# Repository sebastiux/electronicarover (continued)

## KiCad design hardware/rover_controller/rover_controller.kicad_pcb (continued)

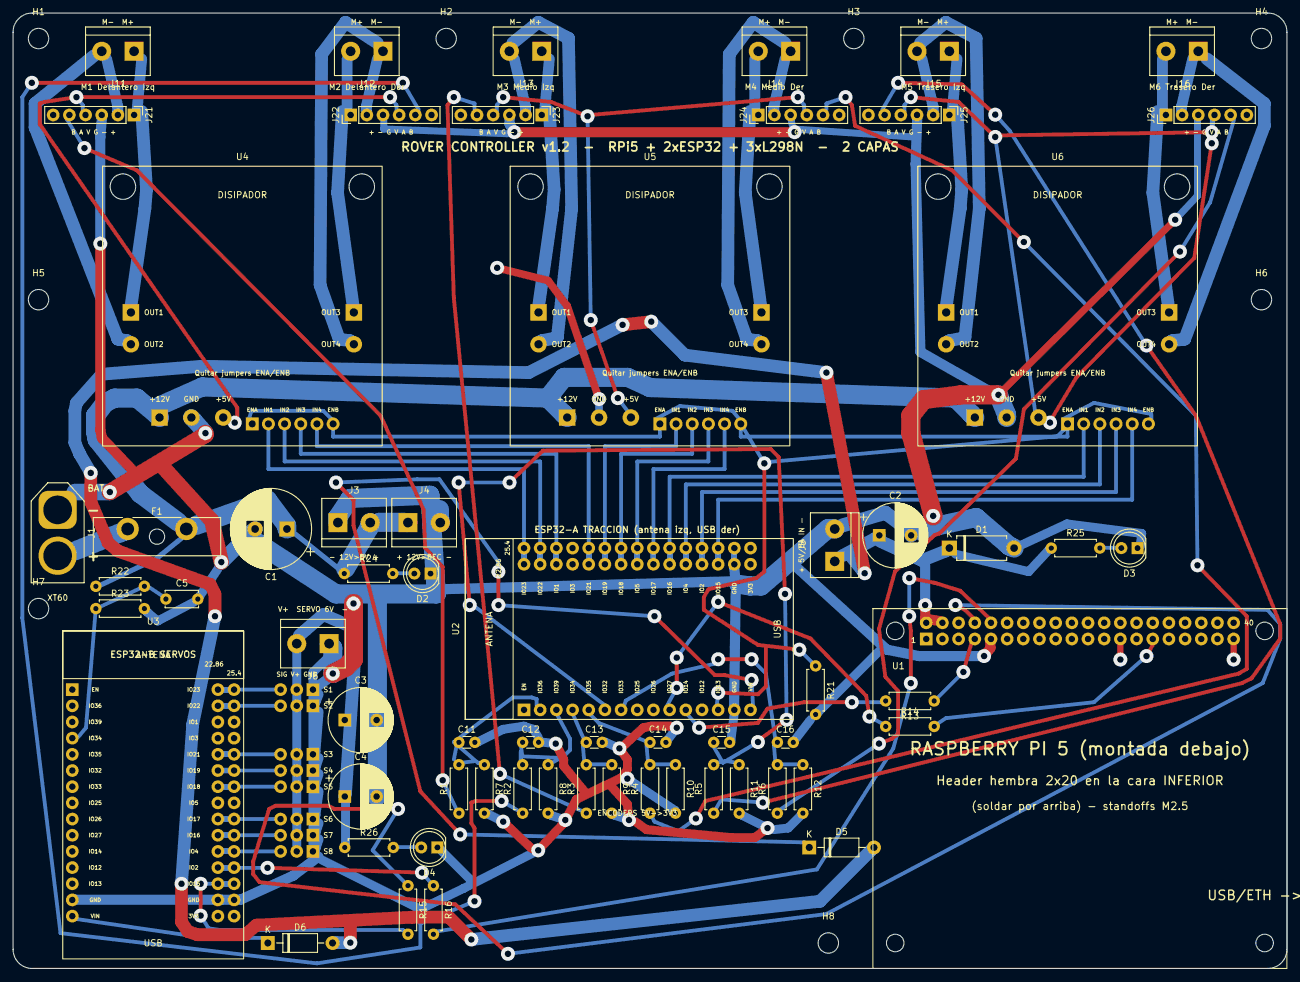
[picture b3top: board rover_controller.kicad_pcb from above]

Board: 2 copper layers, 200.0 x 150.0 mm, 79 parts (0 on the bottom side), 67 nets.

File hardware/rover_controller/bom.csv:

Cant;Referencias;Valor;Footprint;Parte sugerida;Descripcion
1;C1;1000uF 25V;Capacitor_THT:CP_Radial_D12.5mm_P5.00mm;1000uF 25V;Bulk VBAT
3;C2,C3,C4;1000uF 10V;Capacitor_THT:CP_Radial_D10.0mm_P5.00mm;1000uF 10V;Bulk 5V
1;C5;100nF;Capacitor_THT:C_Disc_D5.0mm_W2.5mm_P5.00mm;100nF;Filtro ADC VBAT
1;D1;SA5.0A;Diode_THT:D_DO-15_P10.16mm_Horizontal;SA5.0A DO-15;TVS 5V (proteccion Pi)
1;D2;LED rojo 12V;LED_THT:LED_D5.0mm;LED 5mm THT tradicional (rojo);Indicador 12V
1;D3;LED verde 5V;LED_THT:LED_D5.0mm;LED 5mm THT tradicional (verde);Indicador 5V
1;D4;LED azul SERVO;LED_THT:LED_D5.0mm;LED 5mm THT tradicional (azul);Indicador rail servos
1;F1;ATO 15A;Fuse:Fuseholder_Blade_ATO_Littelfuse_Pudenz_2_Pin;Littelfuse/Pudenz 2 pin ATO holder;Portafusible ATO para PCB + fusible 15A
8;H1,H2,H3,H4,H5,H6,H7,H8;M3;MountingHole:MountingHole_3.2mm_M3;M3;Agujero de montaje M3
1;J1;XT60 BAT 12V;Connector_AMASS:AMASS_XT60-M_1x02_P7.20mm_Vertical;AMASS XT60 macho (copas para soldar) / XT60-M;Conector XT60 macho para bateria LiPo 3S (lado biselado = -)
1;J11;Motor M1;TerminalBlock:TerminalBlock_bornier-2_P5.08mm;KF301-2P / DG301 5.08mm;Bornera 2P 5.08mm motor M1 (Delantero Izq)
1;J12;Motor M2;TerminalBlock:TerminalBlock_bornier-2_P5.08mm;KF301-2P / DG301 5.08mm;Bornera 2P 5.08mm motor M2 (Delantero Der)
1;J13;Motor M3;TerminalBlock:TerminalBlock_bornier-2_P5.08mm;KF301-2P / DG301 5.08mm;Bornera 2P 5.08mm motor M3 (Medio Izq)
1;J14;Motor M4;TerminalBlock:TerminalBlock_bornier-2_P5.08mm;KF301-2P / DG301 5.08mm;Bornera 2P 5.08mm motor M4 (Medio Der)
1;J15;Motor M5;TerminalBlock:TerminalBlock_bornier-2_P5.08mm;KF301-2P / DG301 5.08mm;Bornera 2P 5.08mm motor M5 (Trasero Izq)
1;J16;Motor M6;TerminalBlock:TerminalBlock_bornier-2_P5.08mm;KF301-2P / DG301 5.08mm;Bornera 2P 5.08mm motor M6 (Trasero Der)
1;J21;Pololu37D_M1;Connector_PinHeader_2.54mm:PinHeader_1x06_P2.54mm_Vertical;Header macho 1x6 2.54mm;Header 1x6 macho: cable Pololu 37D (M+, M-, GND, VCC, A, B)
1;J22;Pololu37D_M2;Connector_PinHeader_2.54mm:PinHeader_1x06_P2.54mm_Vertical;Header macho 1x6 2.54mm;Header 1x6 macho: cable Pololu 37D (M+, M-, GND, VCC, A, B)
1;J23;Pololu37D_M3;Connector_PinHeader_2.54mm:PinHeader_1x06_P2.54mm_Vertical;Header macho 1x6 2.54mm;Header 1x6 macho: cable Pololu 37D (M+, M-, GND, VCC, A, B)
1;J24;Pololu37D_M4;Connector_PinHeader_2.54mm:PinHeader_1x06_P2.54mm_Vertical;Header macho 1x6 2.54mm;Header 1x6 macho: cable Pololu 37D (M+, M-, GND, VCC, A, B)
1;J25;Pololu37D_M5;Connector_PinHeader_2.54mm:PinHeader_1x06_P2.54mm_Vertical;Header macho 1x6 2.54mm;Header 1x6 macho: cable Pololu 37D (M+, M-, GND, VCC, A, B)
1;J26;Pololu37D_M6;Connector_PinHeader_2.54mm:PinHeader_1x06_P2.54mm_Vertical;Header macho 1x6 2.54mm;Header 1x6 macho: cable Pololu 37D (M+, M-, GND, VCC, A, B)
1;J3;12V OUT -> buck 5V;TerminalBlock:TerminalBlock_bornier-2_P5.08mm;KF301-2P 5.08mm;Salida 12V protegida hacia el step-down de 5V/5A
1;J31;SERVO1;rover:Servo_Header_1x03;Header macho 1x3 2.54mm;Servo 1 - Direccion DI (GND, V+, SIG)
1;J32;SERVO2;rover:Servo_Header_1x03;Header macho 1x3 2.54mm;Servo 2 - Direccion DD (GND, V+, SIG)
1;J33;SERVO3;rover:Servo_Header_1x03;Header macho 1x3 2.54mm;Servo 3 - Direccion TI (GND, V+, SIG)
1;J34;SERVO4;rover:Servo_Header_1x03;Header macho 1x3 2.54mm;Servo 4 - Direccion TD (GND, V+, SIG)
1;J35;SERVO5;rover:Servo_Header_1x03;Header macho 1x3 2.54mm;Servo 5 - Brazo base (GND, V+, SIG)
1;J36;SERVO6;rover:Servo_Header_1x03;Header macho 1x3 2.54mm;Servo 6 - Brazo hombro (GND, V+, SIG)
1;J37;SERVO7;rover:Servo_Header_1x03;Header macho 1x3 2.54mm;Servo 7 - Brazo pinza (GND, V+, SIG)
1;J38;SERVO8;rover:Servo_Header_1x03;Header macho 1x3 2.54mm;Servo 8 - Reserva (GND, V+, SIG)
1;J4;12V OUT -> BEC servos;TerminalBlock:TerminalBlock_bornier-2_P5.08mm;KF301-2P 5.08mm;Salida 12V protegida hacia el BEC de servos 6V
1;J43;AUX RPi (I2C);Connector_PinHeader_2.54mm:PinHeader_1x08_P2.54mm_Vertical;Header macho 1x8;Header auxiliar Raspberry Pi (I2C + GPIO)
1;J5;5V IN (buck 5V 5A);TerminalBlock:TerminalBlock_bornier-2_P5.08mm;KF301-2P 5.08mm;Entrada 5V/5A desde step-down (alimenta Pi 5 y ESP32)
1;J6;SERVO PWR IN (6V);TerminalBlock:TerminalBlock_bornier-2_P5.08mm;KF301-2P 5.08mm;Entrada BEC servos 6V
7;R1,R2,R3,R4,R5,R6,R21;10k;Resistor_THT:R_Axial_DIN0207_L6.3mm_D2.5mm_P7.62mm_Horizontal;Resistencia 10k 1/4W (0.25W) THT pelicula metalica/carbon;Divisor encoder (serie)
4;R13,R14,R15,R16;1k;Resistor_THT:R_Axial_DIN0207_L6.3mm_D2.5mm_P7.62mm_Horizontal;Resistencia 1k 1/4W (0.25W) THT pelicula metalica/carbon;Serie UART Pi TXD2 -> ESP32-A RX
1;R22;100k;Resistor_THT:R_Axial_DIN0207_L6.3mm_D2.5mm_P7.62mm_Horizontal;Resistencia 100k 1/4W (0.25W) THT pelicula metalica/carbon;Divisor VBAT (alto)
1;R23;27k;Resistor_THT:R_Axial_DIN0207_L6.3mm_D2.5mm_P7.62mm_Horizontal;Resistencia 27k 1/4W (0.25W) THT pelicula metalica/carbon;Divisor VBAT (bajo)
1;R24;2.2k;Resistor_THT:R_Axial_DIN0207_L6.3mm_D2.5mm_P7.62mm_Horizontal;Resistencia 2.2k 1/4W (0.25W) THT pelicula metalica/carbon;Resistencia LED 12V
1;R25;330;Resistor_THT:R_Axial_DIN0207_L6.3mm_D2.5mm_P7.62mm_Horizontal;Resistencia 330 1/4W (0.25W) THT pelicula metalica/carbon;Resistencia LED 5V
1;R26;470;Resistor_THT:R_Axial_DIN0207_L6.3mm_D2.5mm_P7.62mm_Horizontal;Resistencia 470 1/4W (0.25W) THT pelicula metalica/carbon;Resistencia LED servos
6;R7,R8,R9,R10,R11,R12;20k;Resistor_THT:R_Axial_DIN0207_L6.3mm_D2.5mm_P7.62mm_Horizontal;Resistencia 20k 1/4W (0.25W) THT pelicula metalica/carbon;Divisor encoder (a GND)
1;U1;RaspberryPi5_GPIO;rover:RPi5_HAT_Header_2x20;Stacking header 2x20 2.54mm pines largos;Stacking header 2x20 de pines largos (Pi 5 debajo, soldar por la cara de cobre)
1;U2;ESP32-A_Traccion;rover:ESP32_DevKitV1_30P_DualPitch;ESP32 DevKit V1 CP2102 + 2x header hembra 1x15;ESP32 DevKit V1 30 pines sobre 2x header hembra 1x15
1;U3;ESP32-B_Servos;rover:ESP32_DevKitV1_30P_DualPitch;ESP32 DevKit V1 CP2102 + 2x header hembra 1x15;ESP32 DevKit V1 30 pines sobre 2x header hembra 1x15
3;U4,U5,U6;L298N_Module;rover:L298N_Module_Pins;Modulo puente H L298N (HW-095);Modulo L298N (bornas sustituidas por pines, quitar jumpers ENA/ENB, dejar el jumper 5V-EN: su +5V alimenta los encoders)

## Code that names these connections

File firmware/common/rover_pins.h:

// rover_pins.h - Mapa de pines de la PCB Rover Controller v1.0 (2 capas)
// Fuente: hardware/tools/rover_design.py (mantener sincronizado).
//
// Las asignaciones estan elegidas para que el ruteo de la PCB quede limpio:
// el orden fisico de los pines de la ESP32 coincide con el orden de los
// destinos. Los UART del ESP32 se remapean (Serial2.begin(baud, cfg, RX, TX)).
#pragma once

// ===========================================================================
// ESP32-A : TRACCION (U2, montada horizontal bajo los L298N)
// ===========================================================================
#if defined(ROVER_ESP32_A)

// Habilitacion global de los 6 canales (ENA/ENB de los 3 L298N).
// Pull-down de 10k: los motores quedan APAGADOS hasta que el firmware ponga
// este pin en HIGH (los IN pueden "parpadear" durante el arranque sin efecto).
#define PIN_MOTOR_EN 13

// Control por motor: PWM en un IN y el otro en LOW (EN = HIGH via MOTOR_EN).
//   avance:  IN_A = PWM, IN_B = 0      reversa: IN_A = 0, IN_B = PWM
//   freno:   IN_A = 1,   IN_B = 1      libre:   MOTOR_EN = 0 (afecta a todos)
//                          {IN_A, IN_B}
#define PIN_M1 {23, 22} // U4 IN1/IN2 -> OUT1/OUT2  Delantero Izq
#define PIN_M2 {1, 21}  // U4 IN3/IN4 -> OUT3/OUT4  Delantero Der  (GPIO1 = TX0!)
#define PIN_M3 {19, 18} // U5 IN1/IN2               Medio Izq
#define PIN_M4 {5, 17}  // U5 IN3/IN4               Medio Der
#define PIN_M5 {16, 4}  // U6 IN1/IN2               Trasero Izq
#define PIN_M6 {2, 15}  // U6 IN3/IN4               Trasero Der
// OJO: GPIO1 (TX0) maneja un IN del L298N: NO uses Serial.print() en la
// ESP32-A una vez arrancado el control (usa Serial2 hacia la Pi para telemetria).

// Encoders Pololu 37D, canal A (divisor 10k/20k -> 3.3V). 16 pulsos por vuelta
// del motor por canal x 30 = 480 flancos de subida por vuelta de rueda.
// El canal B no esta cableado; el sentido se toma del comando.
#define PIN_ENC1_A 36
#define PIN_ENC2_A 39
#define PIN_ENC3_A 34
#define PIN_ENC4_A 35
#define PIN_ENC5_A 32
#define PIN_ENC6_A 33

// UART <-> Raspberry Pi (Pi UART2: GPIO4 TX / GPIO5 RX, /dev/ttyAMA2)
#define PIN_UART_RX 14
#define PIN_UART_TX 27
// Serial2.begin(115200, SERIAL_8N1, PIN_UART_RX, PIN_UART_TX);

#endif

// ===========================================================================
// ESP32-B : SERVOS + BRAZO (U3, vertical a la izquierda)
// ===========================================================================
#if defined(ROVER_ESP32_B)

#define PIN_SERVO1 23 // Direccion delantera izq
#define PIN_SERVO2 22 // Direccion delantera der
#define PIN_SERVO3 21 // Direccion trasera izq
#define PIN_SERVO4 19 // Direccion trasera der
#define PIN_SERVO5 18 // Brazo base
#define PIN_SERVO6 17 // Brazo hombro
#define PIN_SERVO7 16 // Brazo pinza
#define PIN_SERVO8 4  // Brazo codo/muneca

// Voltaje de bateria: divisor 100k / 27k (VBAT = Vadc * 127 / 27)
#define PIN_VBAT_SENSE 34
#define VBAT_DIVIDER_RATIO (127.0f / 27.0f)

// UART <-> Raspberry Pi (Pi UART0: GPIO14 TX / GPIO15 RX, /dev/ttyAMA0)
#define PIN_UART_RX 15
#define PIN_UART_TX 2   // GPIO2 tambien enciende el LED azul de la placa
// Serial2.begin(115200, SERIAL_8N1, PIN_UART_RX, PIN_UART_TX);

#endif

// ===========================================================================
// RASPBERRY PI 5 (numeros BCM) - /boot/firmware/config.txt:
//   dtoverlay=uart0-pi5   # GPIO14/15 -> ESP32-B  (/dev/ttyAMA0)
//   dtoverlay=uart2-pi5   # GPIO4/5   -> ESP32-A  (/dev/ttyAMA2)
//   usb_max_current_enable=1
// El resto de los GPIO quedan libres: los pines largos del stacking header
// sobresalen por arriba de la PCB y se puede conectar ahi con cables Dupont.
// ===========================================================================

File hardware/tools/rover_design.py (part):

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    # Otras fuentes dan 36.6 / 37 / 37.2 mm. Barreno de 4.0 mm centrado a +-18.75:
    # con tornillo M3 acepta cualquier separacion entre 36.5 y 38.5 mm.
    # Solo los 2 barrenos del lado del disipador: el lado de los pines queda fijo por
    # los 13 pines soldados (y ahi los barrenos de 4 mm cortarian la pista MOTOR_EN).
    "size": 43.9,
    "mount_holes": [(-18.75, -18.75), (18.75, -18.75)],
    "mount_drill": 4.0,
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}
RPI_PINS = {
    1: "3V3", 2: "5V", 3: "GPIO2/SDA", 4: "5V", 5: "GPIO3/SCL", 6: "GND",
    7: "GPIO4/TXD2", 8: "GPIO14/TXD0", 9: "GND", 10: "GPIO15/RXD0",
    11: "GPIO17", 12: "GPIO18", 13: "GPIO27", 14: "GND", 15: "GPIO22",
    16: "GPIO23", 17: "3V3", 18: "GPIO24", 19: "GPIO10", 20: "GND",
    21: "GPIO9", 22: "GPIO25", 23: "GPIO11", 24: "GPIO8", 25: "GND",
    26: "GPIO7", 27: "ID_SD", 28: "ID_SC", 29: "GPIO5/RXD2", 30: "GND",
    31: "GPIO6", 32: "GPIO12", 33: "GPIO13", 34: "GND", 35: "GPIO19",
    36: "GPIO16", 37: "GPIO26", 38: "GPIO20", 39: "GND", 40: "GPIO21",
}
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
    # ======================= ESP32-A (traccion) =============================
    espa = {i: None for i in range(1, 31)}
    espa[esp_pin_number("VIN")] = "VIN_A"     # via diodo D5 (evita retroalimentar por USB)
    espa[14] = "GND"
    espa[29] = "GND"
    for k, gp in ESPA_IN.items():
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            espa[esp_pin_number(g)] = "U%d_IN%d" % (k + 4, j + 1)
    for m, g in ESPA_ENC.items():
        espa[esp_pin_number(g)] = "ENC%d_A" % m
    espa[esp_pin_number(ESPA_MOTOR_EN)] = "MOTOR_EN"
    espa[esp_pin_number(ESPA_UART_TX)] = "ESPA_TX"
    espa[esp_pin_number(ESPA_UART_RX)] = "ESPA_RX"
    add("U2", "ESP32-A_Traccion", "rover:ESP32_DevKitV1_30P", "rover:ESP32_DevKitV1_30P_DualPitch",
        espa, ESPA_POS, (330.2, 76.2),
        desc="ESP32 DevKit V1 30 pines sobre 2x header hembra 1x15",
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
    # ======================= ESP32-B (servos) ===============================
    espb = {i: None for i in range(1, 31)}
    espb[esp_pin_number("VIN")] = "VIN_B"     # via diodo D6
    espb[14] = "GND"
    espb[29] = "GND"
    for n, (g, _) in SERVOS.items():
        espb[esp_pin_number(g)] = "SERVO%d" % n
    espb[esp_pin_number(ESPB_VBAT)] = "VBAT_SENSE"
    espb[esp_pin_number(ESPB_UART_TX)] = "ESPB_TX"
    espb[esp_pin_number(ESPB_UART_RX)] = "ESPB_RX"
    add("U3", "ESP32-B_Servos", "rover:ESP32_DevKitV1_30P", "rover:ESP32_DevKitV1_30P_DualPitch",
        espb, ESPB_POS, (457.2, 76.2),
        desc="ESP32 DevKit V1 30 pines sobre 2x header hembra 1x15",
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
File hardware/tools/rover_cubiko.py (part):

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    for n in (9, 25, 39):                     # GND de la fila interior (salen hacia abajo)
        pi[n] = "GND"
    pi[7], pi[29] = "PI_TXD2", "PI_RXD2"      # UART2 -> ESP32-A
    pi[32], pi[33] = "PI_TXD4", "PI_RXD4"     # UART4 (GPIO12/13, /dev/ttyAMA4) -> ESP32-B
    add("U1", "RaspberryPi5_GPIO", "rover:RaspberryPi5_GPIO", "rover:RPi5_HAT_Header_2x20",
        pi, (ox, oy, 0), _sch_pos(),
        desc="Header hembra 2x20 en la cara inferior (Pi 5 debajo)", mpn="Header hembra 2x20 2.54mm")

    # ======================= ESP32-A (traccion) =============================
    espa = {i: None for i in range(1, 31)}
    espa[esp_pin_number("VIN")] = "VIN_A"
    espa[14] = espa[29] = "GND"
    for k, gp in ESPA_IN.items():
        for j, g in enumerate(gp):
            espa[esp_pin_number(g)] = "U%d_IN%d" % (k + 4, j + 1)
    for m, g in ESPA_ENC.items():
        espa[esp_pin_number(g)] = "ENC%d_A" % m
    espa[esp_pin_number(ESPA_MOTOR_EN)] = "MOTOR_EN"
    espa[esp_pin_number(ESPA_UART_TX)] = "ESPA_TX"
    espa[esp_pin_number(ESPA_UART_RX)] = "ESPA_RX"
    add("U2", "ESP32-A_Traccion", "rover:ESP32_DevKitV1_30P", "rover:ESP32_DevKitV1_30P_DualPitch",
        espa, ESPA_POS, _sch_pos(), desc="ESP32 DevKit V1 30 pines sobre 2x header hembra 1x15",
        mpn="ESP32 DevKit V1 + 2x header hembra 1x15")

    # ======================= ESP32-B (servos) ===============================
    espb = {i: None for i in range(1, 31)}
    espb[esp_pin_number("VIN")] = "VIN_B"
    espb[14] = espb[29] = "GND"
    for n, (g, _) in SERVOS.items():
        espb[esp_pin_number(g)] = "SERVO%d" % n
    espb[esp_pin_number(ESPB_VBAT)] = "VBAT_SENSE"
    espb[esp_pin_number(ESPB_UART_TX)] = "ESPB_TX"
    espb[esp_pin_number(ESPB_UART_RX)] = "ESPB_RX"
    add("U3", "ESP32-B_Servos", "rover:ESP32_DevKitV1_30P", "rover:ESP32_DevKitV1_30P_DualPitch",
        espb, ESPB_POS, _sch_pos(), desc="ESP32 DevKit V1 30 pines sobre 2x header hembra 1x15",
        mpn="ESP32 DevKit V1 + 2x header hembra 1x15")
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
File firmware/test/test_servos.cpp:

// Simulacion firmware ESP32-B (servos + bateria) sobre el netlist real de la PCB.
#include "Arduino.h"
#include "../servos/src/main.cpp"
#include "testlib.h"

static const char* ESP = "U3";
static void run_ms(int ms) { for (int t = 0; t < ms; ++t) { ++sim::now_ms; loop(); } }
static double pulse_us(int gpio) {
  auto& p = sim::pins[gpio];
  return p.pwm ? p.duty * (1e6 / p.freq) / ((1u << p.bits) - 1) : 0;
}

int main() {
  printf("Simulacion ESP32-B (servos) sobre el netlist de rover_controller.kicad_pcb\n");
  setup();

  section("UART con la Raspberry Pi");
  check_uart_path(ESP, Serial2.rx_pin, Serial2.tx_pin);

  section("Servos: GPIO -> header (GND, V+, SIG)");
  for (int n = 1; n <= 8; ++n) {
    int g = SERVO_PINS[n - 1];
    std::string net = sb::esp_net(ESP, g), hdr;
    for (auto& rp : sb::on_net(net)) if (rp.first[0] == 'J' && rp.second == "3") hdr = rp.first;
    bool pinout = !hdr.empty() && sb::net(hdr, "1") == "GND" && sb::net(hdr, "2") == "SERVO_V";
    CHECK(pinout && sb::value(hdr) == "SERVO" + std::to_string(n),
          "S%d: GPIO%d -> %s -> %s pin3 (SIG); pin1=%s pin2=%s", n, g, net.c_str(), hdr.c_str(),
          sb::net(hdr, "1").c_str(), sb::net(hdr, "2").c_str());
    CHECK(std::fabs(pulse_us(g) - 1500) < 2 && sim::pins[g].freq == 50, "S%d: arranca centrado (%.0f us @ %u Hz)", n, pulse_us(g), sim::pins[g].freq);
    Serial2.inject("A " + std::to_string(n) + " 0\n"); run_ms(2);
    double a0 = pulse_us(g);
    Serial2.inject("A " + std::to_string(n) + " 180\n"); run_ms(2);
    double a180 = pulse_us(g);
    Serial2.inject("S " + std::to_string(n) + " 5000\n"); run_ms(2);
    double lim = pulse_us(g);
    CHECK(std::fabs(a0 - 800) < 2 && std::fabs(a180 - 2200) < 2 && std::fabs(lim - 2200) < 2,
          "S%d: 0 grados=%.0f us, 180 grados=%.0f us, 5000 us se limita a %.0f us", n, a0, a180, lim);
  }

  section("Voltaje de bateria (XT60 -> fusible -> divisor -> ADC)");
  std::string sense = sb::esp_net(ESP, PIN_VBAT_SENSE);
  double rtop = 0, rbot = 0; std::string rt, rb;
  for (auto& rp : sb::on_net(sense)) {
    if (!sb::is_res(rp.first)) continue;
    std::string o = sb::other_end(rp.first, rp.second);
    if (o == "VBAT_F") { rtop = sb::ohms(rp.first); rt = rp.first; }
    if (o == "GND") { rbot = sb::ohms(rp.first); rb = rp.first; }
  }
  CHECK(rtop > 0 && rbot > 0, "GPIO%d -> %s: %s(%s) a VBAT_F y %s(%s) a GND", PIN_VBAT_SENSE, sense.c_str(),
        rt.c_str(), sb::value(rt).c_str(), rb.c_str(), sb::value(rb).c_str());
  for (double vbat : {9.0, 11.1, 12.6, 14.4}) {
    double vadc = vbat * rbot / (rtop + rbot);
    sim::pins[PIN_VBAT_SENSE].adc_mv = (uint32_t)(vadc * 1000 + 0.5);
    Serial2.out.clear(); Serial2.inject("?\n"); run_ms(2);
    auto v = nums(last_line(Serial2.out, "B"));
    double rep = v.empty() ? 0 : v[0] / 1000.0;
    bool low_ok = v.size() >= 2 && (v[1] == (vbat < 9.9 ? 1 : 0));
    CHECK(std::fabs(rep - vbat) < 0.05 * vbat && vadc < 3.1 && low_ok,
          "VBAT %.1f V -> ADC %.2f V (max 3.1 V) -> reporta %.2f V, alarma=%ld", vbat, vadc, rep, v.size() >= 2 ? v[1] : -1);
  }

  section("Alimentacion de las ESP32 (diodos Schottky en VIN)");
  for (const char* e : {"U2", "U3"}) {
    std::string vin = sb::net(e, "15");
    if (vin.empty()) continue;   // tarjeta de servos separada: solo lleva la ESP32-B
    std::string d;
    for (auto& rp : sb::on_net(vin)) if (rp.first[0] == 'D') d = rp.first;
    bool ok = !d.empty() && sb::net(d, "1") == vin && sb::net(d, "2") == "+5V";
    CHECK(ok, "%s VIN=%s <- %s (catodo en VIN, anodo en +5V) %s", e, vin.c_str(), d.c_str(), sb::value(d).c_str());
  }

  section("Restricciones del ESP32");
  check_strapping(ESP);
  CHECK(sim::errors.empty(), "sin usos ilegales de GPIO en el firmware (%zu)", sim::errors.size());
  for (auto& e : sim::errors) printf("         - %s\n", e.c_str());
  printf("\nRESULTADO ESP32-B: %d OK, %d FALLAS\n", g_pass, g_fail);
  return g_fail ? 1 : 0;
}
